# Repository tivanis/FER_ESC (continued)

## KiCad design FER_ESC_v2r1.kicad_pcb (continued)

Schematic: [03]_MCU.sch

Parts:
C65, C66, C69, C72, C75, C78: 2.2uF, 16V; C_0805_2012Metric; Manufacturer Part Number CL10A225KO8NNNC
C67, C68, C70, C71: 10uF, 16V; C_0805_2012Metric; Manufacturer Part Number EMK212BBJ106MGHT
C73, C74, C76, C77, C79, C80, C81, C82, C85: 100nF, 25V; C_0603_1608Metric; Manufacturer Part Number C0603C104Z3VACTU
C83, C84: 30pF, 5%; C_0402_1005Metric; Manufacturer Part Number AC0402JRNPO9BN300
D10: LED GREEN; LED_0603_1608Metric_Castellated; Manufacturer Part Number 155060VS75300
FB1: 60Ohm @100MHz; L_0805_2012Metric; Manufacturer Part Number BKP2125HS600-T
J5: Conn_01x04; PinHeader_1x04_P2.54mm_Vertical; Manufacturer Part Number 22-28-4041
J6: Conn_02x05_Odd_Even; PinHeader_2x05_P2.54mm_Vertical; Manufacturer Part Number 87914-1026
R74: 0 Ohm; R_0603_1608Metric; Manufacturer Part Number AC0603JR-100RL
R75, R76: 2k; R_0603_1608Metric; Manufacturer Part Number CR0603-FX-2001ELF
R77, R78, R79, R80, R81, R82, R83: 3.3k, 1%; R_0603_1608Metric; Manufacturer Part Number CR0603-FX-3301ELF
SW1: SW_Push; SW_Push_SPST_NO_Alps_SKRK; Manufacturer Part Number SKRKAEE020
U10: TMS320F280049PZS; TQFP-100_14x14mm_P0.5mm; Manufacturer Part Number TMS320F280049PZS
Y1: XTAL; Crystal_SMD_ECS_CSM3X-2Pin_7.6x4.1mm; Manufacturer Part Number ABLS7M-20.000MHZ-B-2-T

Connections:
+1V2: C67.1, C70.1, C73.2, C76.2, C79.2, C81.2, U10.4 (VDD), U10.46 (VDD), U10.71 (VDD), U10.87 (VDD); also elsewhere on the board
/[01]_powerStage/HVDC_SENSE: U10.44 (C14); also elsewhere on the board
/[01]_powerStage/VSENSE_U: U10.31 (C3/PGA4_IN); also elsewhere on the board
/[01]_powerStage/VSENSE_V: U10.37 (A8/PGA6_OF); also elsewhere on the board
/[01]_powerStage/VSENSE_W: U10.41 (B0); also elsewhere on the board
/[02]_driver/DRV_EN: U10.55 (GPIO17); also elsewhere on the board
/[02]_driver/FAULT: U10.54 (GPIO16); also elsewhere on the board
/[02]_driver/ISENSE_U: U10.29 (C1); also elsewhere on the board
/[02]_driver/ISENSE_V: U10.36 (A4/B8/PGA2_OF); also elsewhere on the board
/[02]_driver/ISENSE_W: U10.39 (B4/C8/PGA4_OF); also elsewhere on the board
/[02]_driver/PWM_AH: U10.79 (GPIO0); also elsewhere on the board
/[02]_driver/PWM_AL: U10.78 (GPIO1); also elsewhere on the board
/[02]_driver/PWM_BH: U10.77 (GPIO2); also elsewhere on the board
/[02]_driver/PWM_BL: U10.76 (GPIO3); also elsewhere on the board
/[02]_driver/PWM_CH: U10.75 (GPIO4); also elsewhere on the board
/[02]_driver/PWM_CL: U10.89 (GPIO5); also elsewhere on the board
/[02]_driver/SPIA_CLK: U10.90 (GPIO9); also elsewhere on the board
/[02]_driver/SPIA_MISO: U10.93 (GPIO10); also elsewhere on the board
/[02]_driver/SPIA_MOSI: U10.74 (GPIO8); also elsewhere on the board
/[02]_driver/~SPIA_CS: U10.52 (GPIO11); also elsewhere on the board
/[03]_MCU/ANALOG_IN: U10.6 (A6/PGA5_OF); also elsewhere on the board
/[03]_MCU/BOOTCONF0: R77.2, U10.64 (GPIO32)
/[03]_MCU/BOOTCONF1: R78.1, U10.56 (GPIO24)
/[03]_MCU/CAN_RX: U10.98 (GPIO30); also elsewhere on the board
/[03]_MCU/CAN_STB: U10.94 (GPIO34); also elsewhere on the board
/[03]_MCU/CAN_TX: U10.99 (GPIO31); also elsewhere on the board
/[03]_MCU/CONFIGA: R82.1, R83.2, U10.57 (GPIO25)
/[03]_MCU/EQEP_STB: R79.2, U10.92 (GPIO59)
/[03]_MCU/GPIO_OUT0: J5.3, U10.81 (GPIO23_VSW)
/[03]_MCU/GPIO_OUT1: J5.2, U10.83 (GPIO22_VFBSW)
/[03]_MCU/I2CA_SCL: U10.59 (GPIO27)
/[03]_MCU/I2CA_SDA: U10.58 (GPIO26)
/[03]_MCU/SCIA_RX: U10.1 (GPIO28); also elsewhere on the board
/[03]_MCU/SCIA_TX: U10.100 (GPIO29); also elsewhere on the board
/[03]_MCU/SPIB_CLK: U10.96 (GPIO14); also elsewhere on the board
/[03]_MCU/SPIB_MISO: U10.97 (GPIO6); also elsewhere on the board
/[03]_MCU/SPIB_MOSI: U10.84 (GPIO7); also elsewhere on the board
/[03]_MCU/STATUS_LED: D10.2 (A), U10.91 (GPIO39)
/[03]_MCU/TCK: J6.4, U10.60 (TCK)
/[03]_MCU/TDI: J6.8, U10.63 (GPIO35/TDI)
/[03]_MCU/TDO: J6.6, U10.61 (GPIO37/TDO)
/[03]_MCU/TMS: J6.2, R80.2, U10.62 (TMS)
/[03]_MCU/VREGENZ: R74.2, R75.2, U10.73 (VREGENZ)
/[03]_MCU/X1: C84.2, U10.68 (GPIO18_X2), Y1.1
/[03]_MCU/X2: C83.2, U10.69 (X1), Y1.2
/[03]_MCU/XDS_RX: J6.3, U10.51 (GPIO12)
/[03]_MCU/XDS_TX: J6.5, U10.50 (GPIO13)
/[03]_MCU/XRSN: C85.2, J6.10, R81.1, SW1.2, U10.2 (XRSN)
/[03]_MCU/~HALL_A: U10.65 (GPIO56); also elsewhere on the board
/[03]_MCU/~HALL_B: U10.66 (GPIO57); also elsewhere on the board
/[03]_MCU/~HALL_C: U10.67 (GPIO58); also elsewhere on the board
/[03]_MCU/~SPIB_CS: U10.95 (GPIO15); also elsewhere on the board
GND: C65.2, C66.2, C67.2, C68.2, C69.2, C70.2, C71.2, C72.2, C73.1, C74.1, C75.2, C76.1, C77.1, C78.2, C79.1, C80.1, C81.1, C82.1, C83.1, C84.1, C85.1, J5.4, J6.9, R75.1, R76.1, R78.2, R79.1, R83.1, SW1.1, U10.5 (VSS), U10.12 (VSSA), U10.13 (PGA5_GND), U10.14 (PGA1_GND), U10.15 (PGA3_GND), U10.26 (VREFLOB/VREFLOC), U10.27 (VREFLOA), U10.32 (PGA2_GND/PGA4_GND/PGA6_GND), U10.33 (VSSA), U10.42 (PGA7_GND), U10.45 (VSS), U10.72 (VSS), U10.82 (VSS_SW), U10.86 (VSS); also elsewhere on the board
unnamed: C66.1, C69.1, C72.1, FB1.1, U10.11 (VDDA), U10.34 (VDDA)
unnamed: C75.1, U10.24 (VREFHIB/VREFHIC)
unnamed: C78.1, U10.25 (VREFHIA)
unnamed: D10.1 (K), R76.2

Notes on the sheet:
25mOhm @DC
Default boot set to: UART (SCI) channel A

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
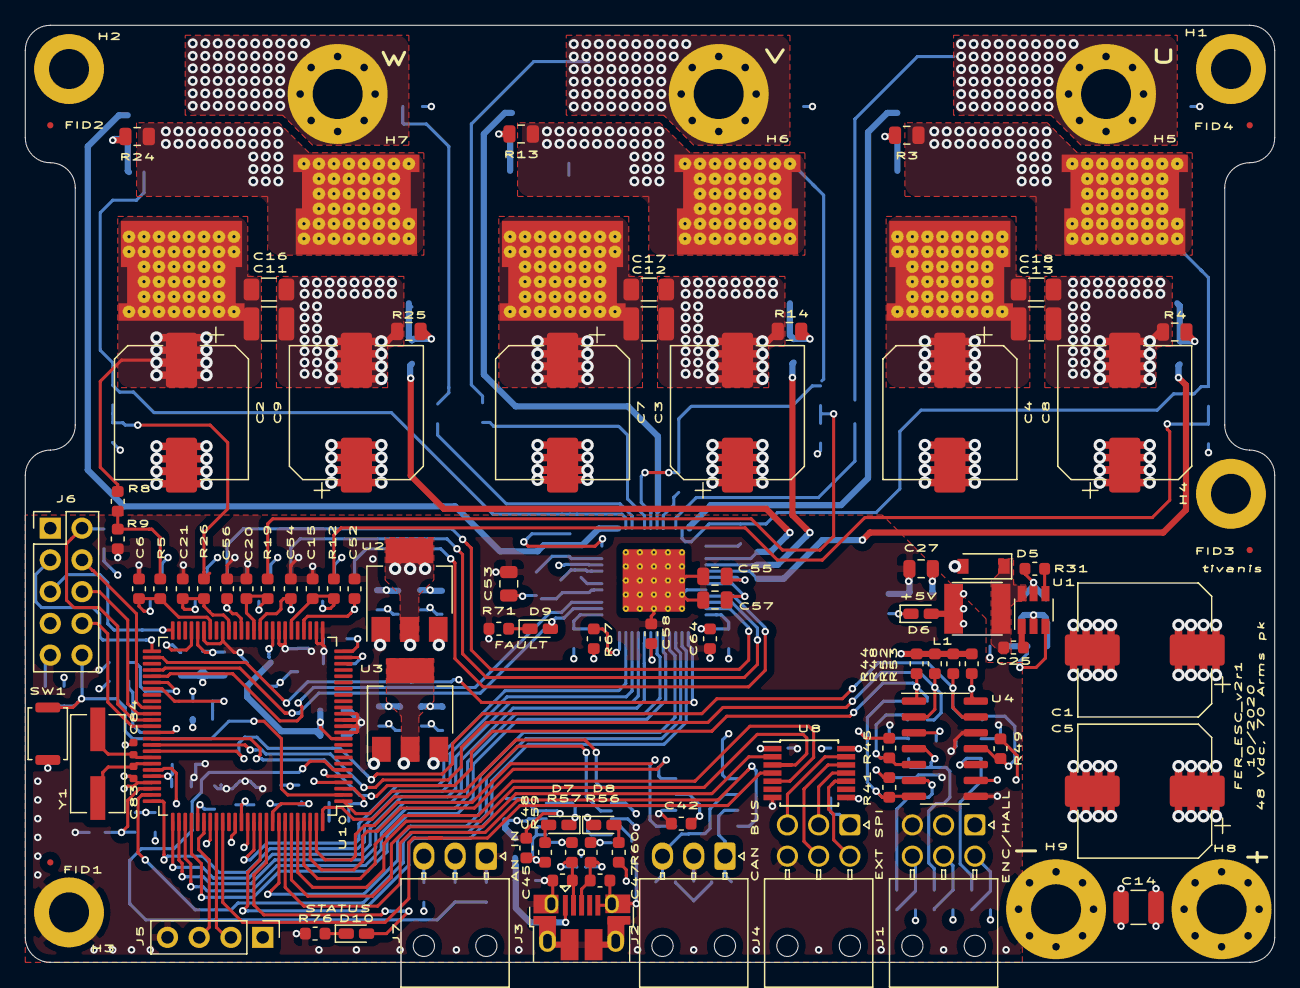
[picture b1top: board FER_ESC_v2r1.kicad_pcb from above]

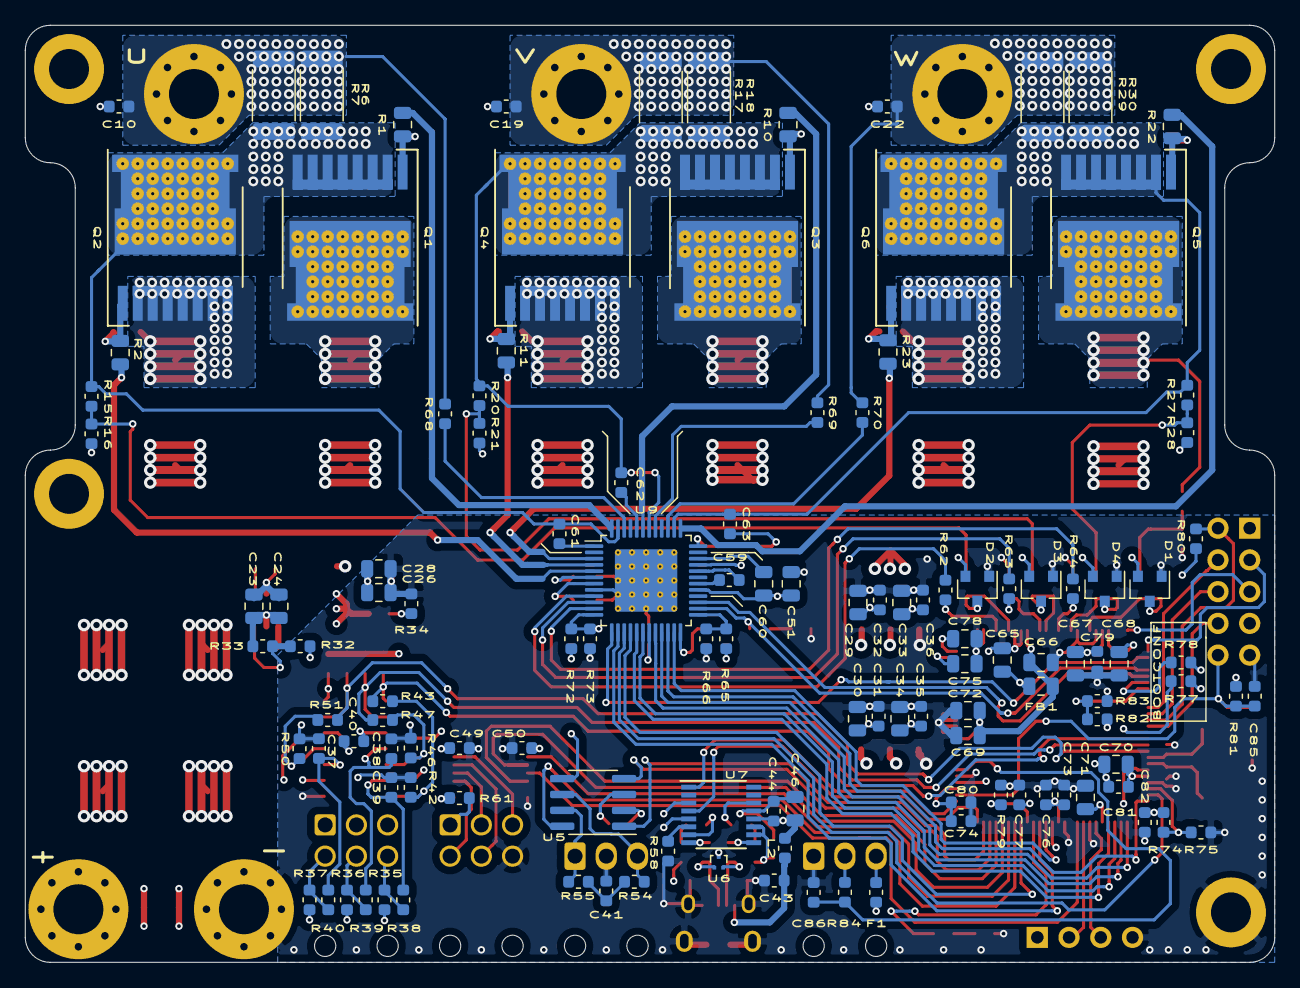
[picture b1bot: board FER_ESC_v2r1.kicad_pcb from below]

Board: 4 copper layers, 100.0 x 75.0 mm, 222 parts (125 on the bottom side), 135 nets.

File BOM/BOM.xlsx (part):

Ref | Qnty | Value | Cmp name | Footprint | Description | Manufacturer Part Number
C6, C15, C20, C21, C25, C32, C36, C31, C35, C40, C42, C48, C44, C43, C50, C49, 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 | 31 | 100nF, 25V | C_Small | Capacitor_SMD:C_0603_1608Metric | Unpolarized capacitor, small symbol | C0603C104Z3VACTU
C7, C8, C9, C3, C4, C5, C2, C1, | 8 | 100uF, 63V | CP | Capacitor_SMD:CP_Elec_10x14.3 | Polarized capacitor | EEH-ZS1J151V
C10, C19, C22, | 3 | 1nF, 100V | C_Small | Capacitor_SMD:C_0603_1608Metric | Unpolarized capacitor, small symbol | C0603C102K1RACTU
C11, C12, C13, C14, | 4 | 10uF, 63V | C_Small | Capacitor_SMD:C_1210_3225Metric | Unpolarized capacitor, small symbol | CL32B106KMVNNWE
C16, C17, C18, | 3 | 0.22uF, 63V | C_Small | Capacitor_SMD:C_1206_3216Metric | Unpolarized capacitor, small symbol | C1206C224MMRECTU
C23, C24, | 2 | 1uF, 100V | C_Small | Capacitor_SMD:C_0805_2012Metric | Unpolarized capacitor, small symbol | GRM21BC72A105KE01L
C26, C27, C46, C55, C57, | 5 | 4.7uF, 25V | C_Small | Capacitor_SMD:C_0805_2012Metric | Unpolarized capacitor, small symbol | 885012107018
C28, | 1 | 1uF, 25V | C_Small | Capacitor_SMD:C_0805_2012Metric | Unpolarized capacitor, small symbol | VJ0805Y105KXXTW1BC
C29, C33, C30, C34, C67, C70, C68, C71, | 8 | 10uF, 16V | C_Small | Capacitor_SMD:C_0805_2012Metric | Unpolarized capacitor, small symbol | EMK212BBJ106MGHT
C37, C38, C39, | 3 | 100pF | C_Small | Capacitor_SMD:C_0603_1608Metric | Unpolarized capacitor, small symbol | 885012206077
C41, | 1 | 10nF, 50V | C_Small | Capacitor_SMD:C_0603_1608Metric | Unpolarized capacitor, small symbol | 885012206089
C45, C47, | 2 | 47pF, 25V | C_Small | Capacitor_SMD:C_0603_1608Metric | Unpolarized capacitor, small symbol | VJ0603A470JXXPW1BC
C53, C60, C51, | 3 | 100nF, 100V | C_Small | Capacitor_SMD:C_0805_2012Metric | Unpolarized capacitor, small symbol | 885012207128
C59, | 1 | 22nF, 100V | C_Small | Capacitor_SMD:C_0603_1608Metric | Unpolarized capacitor, small symbol | C0603C223K1RACTU
C61, C62, C63, | 3 | 470nF, 16V | C_Small | Capacitor_SMD:C_0603_1608Metric | Unpolarized capacitor, small symbol | CC0603JRX7R7BB474
C78, C75, C72, C69, C66, C65, | 6 | 2.2uF, 16V | C_Small | Capacitor_SMD:C_0805_2012Metric | Unpolarized capacitor, small symbol | CL10A225KO8NNNC
C84, C83, | 2 | 30pF, 5% | C_Small | Capacitor_SMD:C_0402_1005Metric | Unpolarized capacitor, small symbol | AC0402JRNPO9BN300
D1, D2, D3, D4, | 4 | BAT54S | BAT54S | Package_TO_SOT_SMD:SOT-23 | schottky barrier diode | BAT54S-TP
D5, | 1 | RB168MM100TFTR | D_Schottky_Small | Diode_SMD:D_SOD-123 | Schottky diode, small symbol | RB168MM100TFTR
D6, D7, D8, D10, | 4 | LED GREEN | LED | LED_SMD:LED_0603_1608Metric_Castellated | Light emitting diode | 155060VS75300
D9, | 1 | LED, RED | LED | LED_SMD:LED_0603_1608Metric_Castellated | Light emitting diode | 150060RS75000
F1, | 1 | Fuse_Small | Fuse_Small | Fuse:Fuse_0603_1608Metric | Fuse, small symbol | F0603G0R15FNTR
FB1, | 1 | 60Ohm @100MHz | Ferrite_Bead_Small | Inductor_SMD:L_0805_2012Metric | Ferrite bead, small symbol | BKP2125HS600-T
FID1, FID3, FID2, FID4, | 4 | Fiducial | Fiducial | Fiducial:Fiducial_0.5mm_Mask1.5mm | Fiducial Marker
H4, H2, H3, H1, | 4 | MountingHole_Pad | MountingHole_Pad | MountingHole:MountingHole_3.2mm_M3_DIN965_Pad | Mounting Hole with connection
H7, H6, H5, | 3 | MountingHole_Pad | MountingHole_Pad | MountingHole:MountingHole_4mm_Pad_Via | Mounting Hole with connection
H8, | 1 | +BATT | MountingHole_Pad | MountingHole:MountingHole_4mm_Pad_Via | Mounting Hole with connection
H9, | 1 | GND | MountingHole_Pad | MountingHole:MountingHole_4mm_Pad_Via | Mounting Hole with connection
J1, J4, | 2 | Conn_02x03_Odd_Even | Conn_02x03_Top_Bottom | Connector_Molex:Molex_Nano-Fit_105314-xx06_2x03_P2.50mm_Horizontal | Generic connector, double row, 02x03, top/bottom pin numbering scheme (row 1: 1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 | 105314-1206
J2, J7, | 2 | Conn_01x03_Male | Conn_01x03 | Connector_Molex:Molex_Nano-Fit_105313-xx03_1x03_P2.50mm_Horizontal | Generic connector, single row, 01x03, script generated (kicad-library-utils/sch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 | 105313-1203
J3, | 1 | USB_B_Micro | USB_B_Micro | Connector_USB:USB_Micro-B_Amphenol_10103594-0001LF_Horizontal | USB Micro Type B connector | 10103594-0001LF
J5, | 1 | Conn_01x04 | Conn_01x04 | Connector_PinHeader_2.54mm:PinHeader_1x04_P2.54mm_Vertical | Generic connector, single row, 01x04, script generated (kicad-library-utils/sch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 | 22-28-4041
J6, | 1 | Conn_02x05_Odd_Even | Conn_02x05_Odd_Even | Connector_PinHeader_2.54mm:PinHeader_2x05_P2.54mm_Vertical | Generic connector, double row, 02x05, odd/even pin numbering scheme (row 1 odd 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 | 87914-1026
L1, | 1 | 6.8uH, 1.6A | L_Core_Ferrite | FER_ZESA_FP:L_Taiyo-Yuden_NR-40xx_HandSoldering_ALT | Inductor with ferrite core | TYS40306R8M-10
L2, | 1 | MH1608-300Y | L_Core_Ferrite_Small | Inductor_SMD:L_0603_1608Metric | Inductor with ferrite core, small symbol | MH1608-300Y
Q3, Q5, Q6, Q4, Q1, Q2, | 6 | IPT007N06N | Q_NMOS_GSD | Package_TO_SOT_SMD:Infineon_PG-HSOF-8-1_ThermalVias | N-MOSFET transistor, gate/source/drain | NVBLS001N06C
R1, R2, R10, R11, R22, R23, | 6 | 6.2 Ohm | R_Small | Resistor_SMD:R_0805_2012Metric | Resistor, small symbol | ERJ-P06J6R2V
R5, R12, R19, R26, R62, R63, R64, R84, | 8 | 39 Ohm | R_Small | Resistor_SMD:R_0603_1608Metric | Resistor, small symbol | CR0603-FX-39R0ELF
R8, R15, R20, R27, | 4 | 44.2k, 1% | R_Small | Resistor_SMD:R_0603_1608Metric | Resistor, small symbol | CR0603-FX-4422ELF
R9, R16, R21, R28, | 4 | 2.4k, 1% | R_Small | Resistor_SMD:R_0603_1608Metric | Resistor, small symbol | CR0603-FX-2401ELF
R25, R24, R14, R13, R4, R3, | 6 | 22k | R_Small | Resistor_SMD:R_0805_2012Metric | Resistor, small symbol | ERJ-PA3J223V
R30, R29, R18, R17, R7, R6, | 6 | 3 mOhm | R_Small | Resistor_SMD:R_2512_6332Metric | Resistor, small symbol | CSS2H-2512K-3L00FE
R31, | 1 | 100k | R_Small | Resistor_SMD:R_0603_1608Metric | Resistor, small symbol | CR0603-FX-1003ELF
R32, | 1 | 55.6k, 0.1% | R_Small | Resistor_SMD:R_0603_1608Metric | Resistor, small symbol | RN731JTTD5562B25
R33, R72, R73, | 3 | 10k, 0.1% | R_Small | Resistor_SMD:R_0603_1608Metric | Resistor, small symbol | ERA-3AEB103V
R34, R59, R60, R71, | 4 | 330 Ohm | R_Small | Resistor_SMD:R_0603_1608Metric | Resistor, small symbol | CR0603-FX-3300ELF
R37, R36, R35, R76, R75, | 5 | 2k | R_Small | Resistor_SMD:R_0603_1608Metric | Resistor, small symbol | CR0603-FX-2001ELF
R38, R40, R39, | 3 | 4.7k | R_Small | Resistor_SMD:R_0603_1608Metric | Resistor, small symbol | CR0603-FX-4701ELF
R41, R45, R49, | 3 | 13k, 1% | R_Small | Resistor_SMD:R_0603_1608Metric | Resistor, small symbol | CR0603-FX-1302ELF
R42, R46, R50, | 3 | 13,3k, 1% | R_Small | Resistor_SMD:R_0603_1608Metric | Resistor, small symbol | CR0603-FX-1332ELF
R43, R47, R51, | 3 | 200k, 1% | R_Small | Resistor_SMD:R_0603_1608Metric | Resistor, small symbol | CR0603-FX-2003ELF
R44, R48, R52, R53, R81, R82, R83, R79, R77, R78, R80, | 11 | 3.3k, 1% | R_Small | Resistor_SMD:R_0603_1608Metric | Resistor, small symbol | CR0603-FX-3301ELF
R54, R55, | 2 | 60.4R | R_Small | Resistor_SMD:R_0603_1608Metric | Resistor, small symbol | ERJ-3EKF60R4V
R56, R57, | 2 | 27R | R_Small | Resistor_SMD:R_0603_1608Metric | Resistor, small symbol | CR0603-FX-27R0ELF
R58, R61, R65, | 3 | 10k | R_Small | Resistor_SMD:R_0603_1608Metric | Resistor, small symbol | CR0603-FX-1002ELF
R66, R67, R74, | 3 | 0 Ohm | R_Small | Resistor_SMD:R_0603_1608Metric | Resistor, small symbol | AC0603JR-100RL
R70, R69, R68, | 3 | 10 Ohm | R_Small | Resistor_SMD:R_0603_1608Metric | Resistor, small symbol | CR0603AFX-10R0EAS
SW1, | 1 | SW_Push | SW_Push | Button_Switch_SMD:SW_Push_SPST_NO_Alps_SKRK | Push button switch, generic, two pins | SKRKAEE020
U1, | 1 | LMR16006XDDCR | LMR16006XDDCR | Package_TO_SOT_SMD:TSOT-23-6 | Voltage Regulators - Switching Regulators LMR16006 SIMPLE SWIT 60V Buck | LMR16006XDDCR
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
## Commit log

2021-03-23 Initial FER_ESC_v2r1 project
2021-03-23 Removed relief from DC input
